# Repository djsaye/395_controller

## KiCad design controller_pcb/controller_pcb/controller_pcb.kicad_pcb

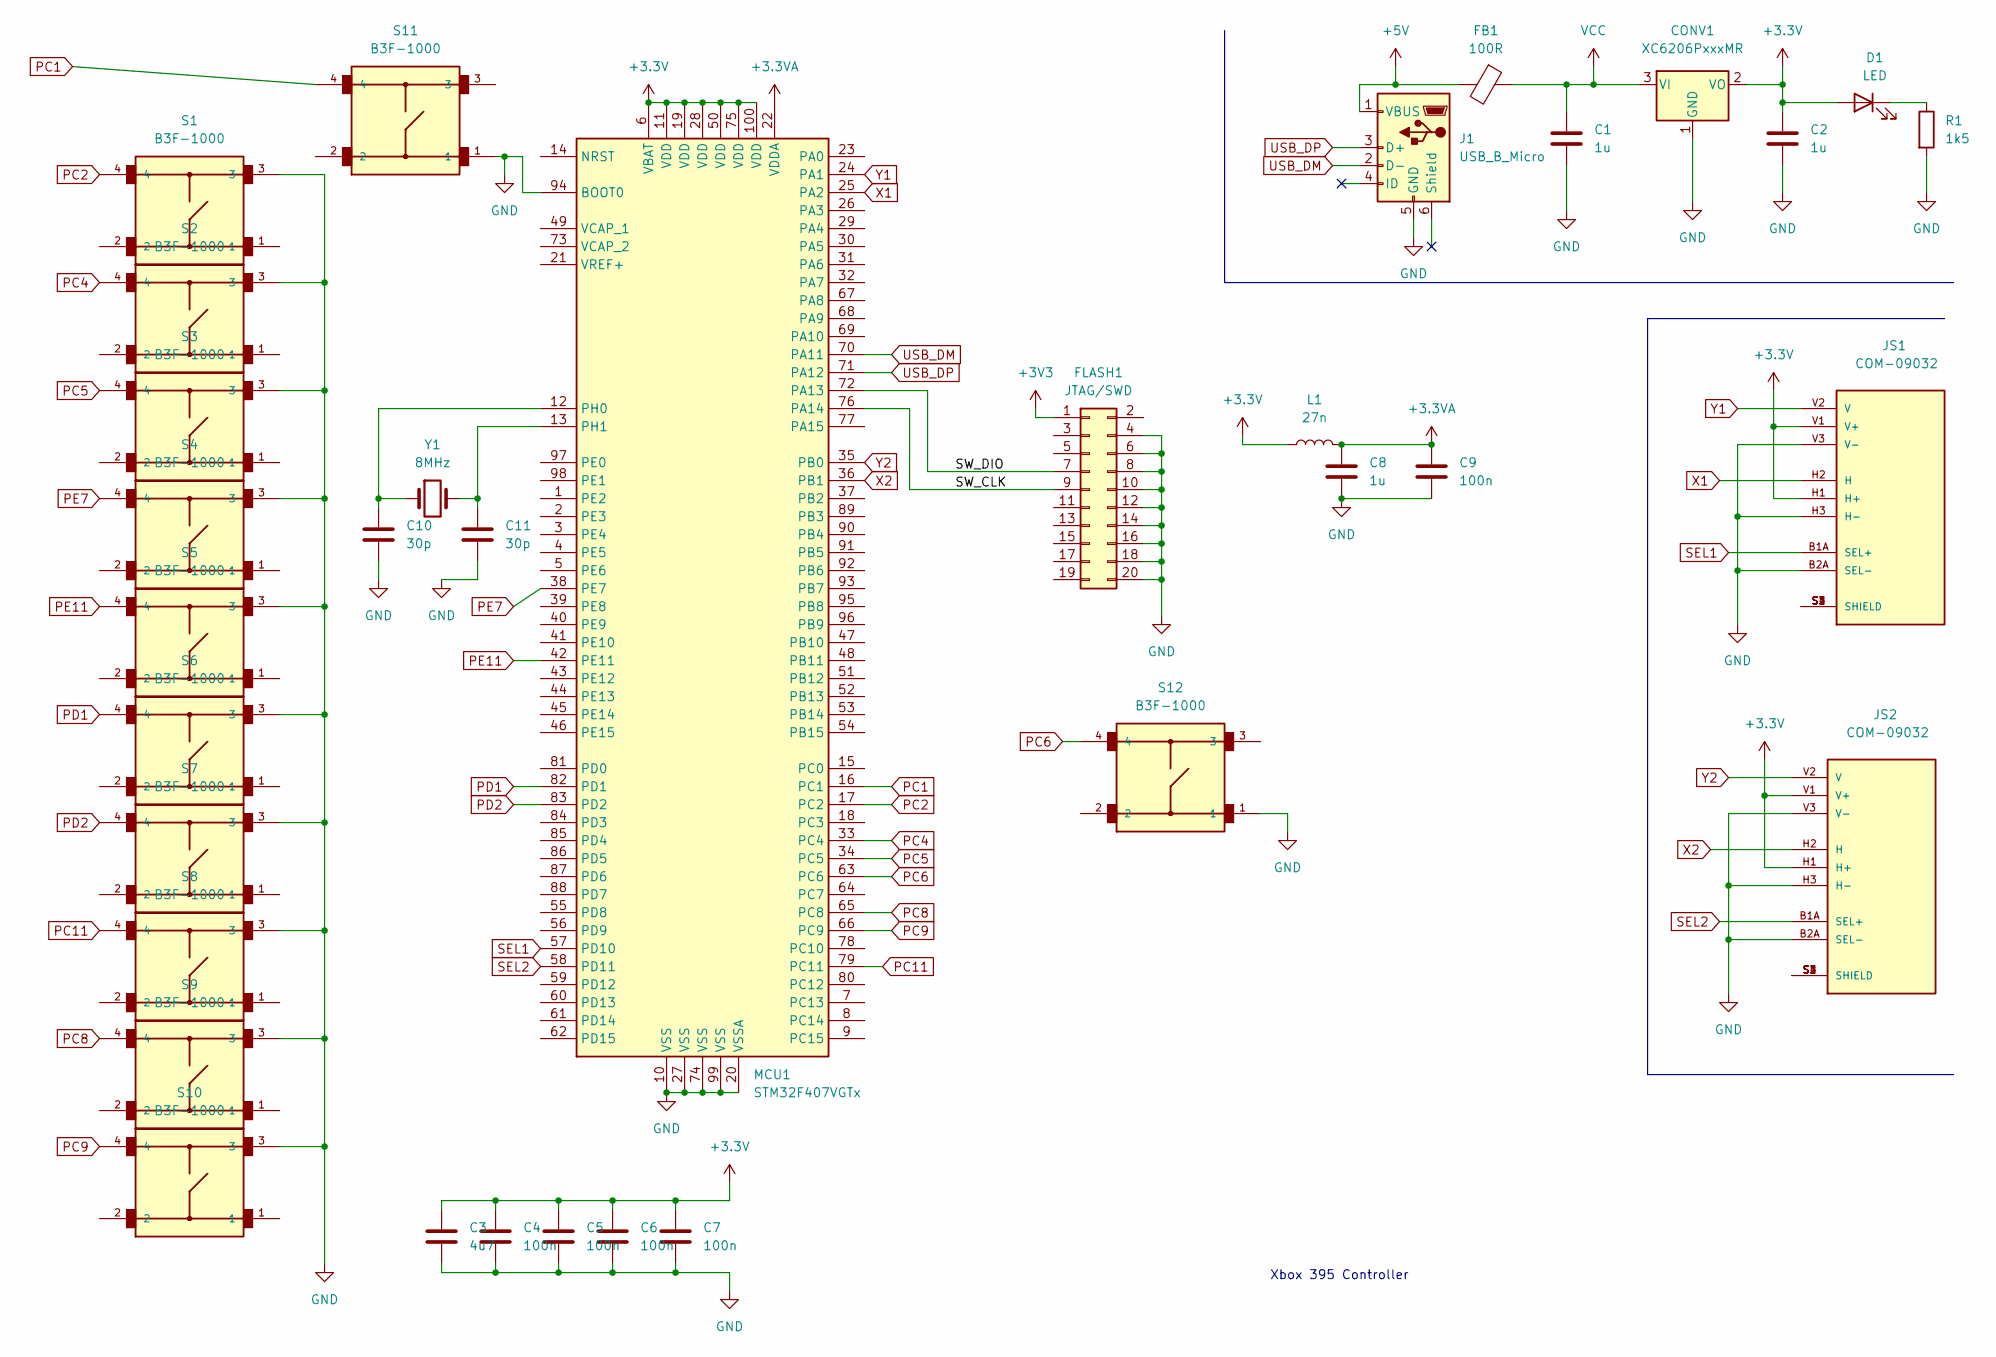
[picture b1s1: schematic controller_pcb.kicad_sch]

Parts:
C1, C2, C8: 1u; C_0805_2012Metric
C3: 4u7; C_0805_2012Metric
C4, C5, C6, C7, C9: 100n; C_0805_2012Metric
C10, C11: 30p; C_0805_2012Metric
CONV1: XC6206PxxxMR; SOT-23
D1: LED; D_0603_1608Metric
FB1: 100R; R_0805_2012Metric
FLASH1: JTAG/SWD; PinHeader_2x10_P2.54mm_Vertical
J1: USB_B_Micro; USB_Micro-B_Wuerth_629105150521
JS1, JS2: COM-09032; XDCR_COM-09032; PARTREV N/A
L1: 27n; L_0402_1005Metric
MCU1: STM32F407VGTx; LQFP-100_14x14mm_P0.5mm
R1: 1k5; R_0805_2012Metric
S1, S2, S3, S4, S5, S6, S7, S8, S9, S10, S11, S12: B3F-1000; SW_B3F-1000
Y1: 8MHz; Crystal_SMD_5032-2Pin_5.0x3.2mm

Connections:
+3.3VA: C8.1, C9.1, L1.2, MCU1.22 (VDDA)
+5V: FB1.2, J1.1 (VBUS)
/SW_CLK: FLASH1.9, MCU1.76 (PA14)
/SW_DIO: FLASH1.7, MCU1.72 (PA13)
GND: C1.2, C2.2, C3.2, C4.2, C5.2, C6.2, C7.2, C8.2, C9.2, C10.2, C11.2, CONV1.1 (GND), FLASH1.4, FLASH1.6, FLASH1.8, FLASH1.10, FLASH1.12, FLASH1.14, FLASH1.16, FLASH1.18, FLASH1.20, J1.5 (GND), JS1.B2A (SEL-), JS1.H3 (H-), JS1.V3 (V-), JS2.B2A (SEL-), JS2.H3 (H-), JS2.V3 (V-), MCU1.10 (VSS), MCU1.20 (VSSA), MCU1.27 (VSS), MCU1.74 (VSS), MCU1.94 (BOOT0), MCU1.99 (VSS), R1.2, S1.3, S2.3, S3.3, S4.3, S5.3, S6.3, S7.3, S8.3, S9.3, S10.3, S11.1, S12.1
unnamed: C10.1, MCU1.12 (PH0), Y1.1
unnamed: C11.1, MCU1.13 (PH1), Y1.2
unnamed: D1.1 (K), R1.1
unnamed: JS1.S1 (SHIELD), JS1.S2 (SHIELD), JS1.S3 (SHIELD), JS1.S4 (SHIELD)
unnamed: JS2.S1 (SHIELD), JS2.S2 (SHIELD), JS2.S3 (SHIELD), JS2.S4 (SHIELD)
PC1: MCU1.16 (PC1), S11.4
PC2: MCU1.17 (PC2), S1.4
PC4: MCU1.33 (PC4), S2.4
PC5: MCU1.34 (PC5), S3.4
PC6: MCU1.63 (PC6), S12.4
PC8: MCU1.65 (PC8), S9.4
PC9: MCU1.66 (PC9), S10.4
PC11: MCU1.79 (PC11), S8.4
PD1: MCU1.82 (PD1), S6.4
PD2: MCU1.83 (PD2), S7.4
PE7: MCU1.38 (PE7), S4.4
PE11: MCU1.42 (PE11), S5.4
SEL1: JS1.B1A (SEL+), MCU1.57 (PD10)
SEL2: JS2.B1A (SEL+), MCU1.58 (PD11)
USB_DM: J1.2 (D-), MCU1.70 (PA11)
USB_DP: J1.3 (D+), MCU1.71 (PA12)
VCC: C1.1, CONV1.3 (VI), FB1.1
X1: JS1.H2 (H), MCU1.25 (PA2)
X2: JS2.H2 (H), MCU1.36 (PB1)
Y1: JS1.V2 (V), MCU1.24 (PA1)
Y2: JS2.V2 (V), MCU1.35 (PB0)

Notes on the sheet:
Xbox 395 Controller

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
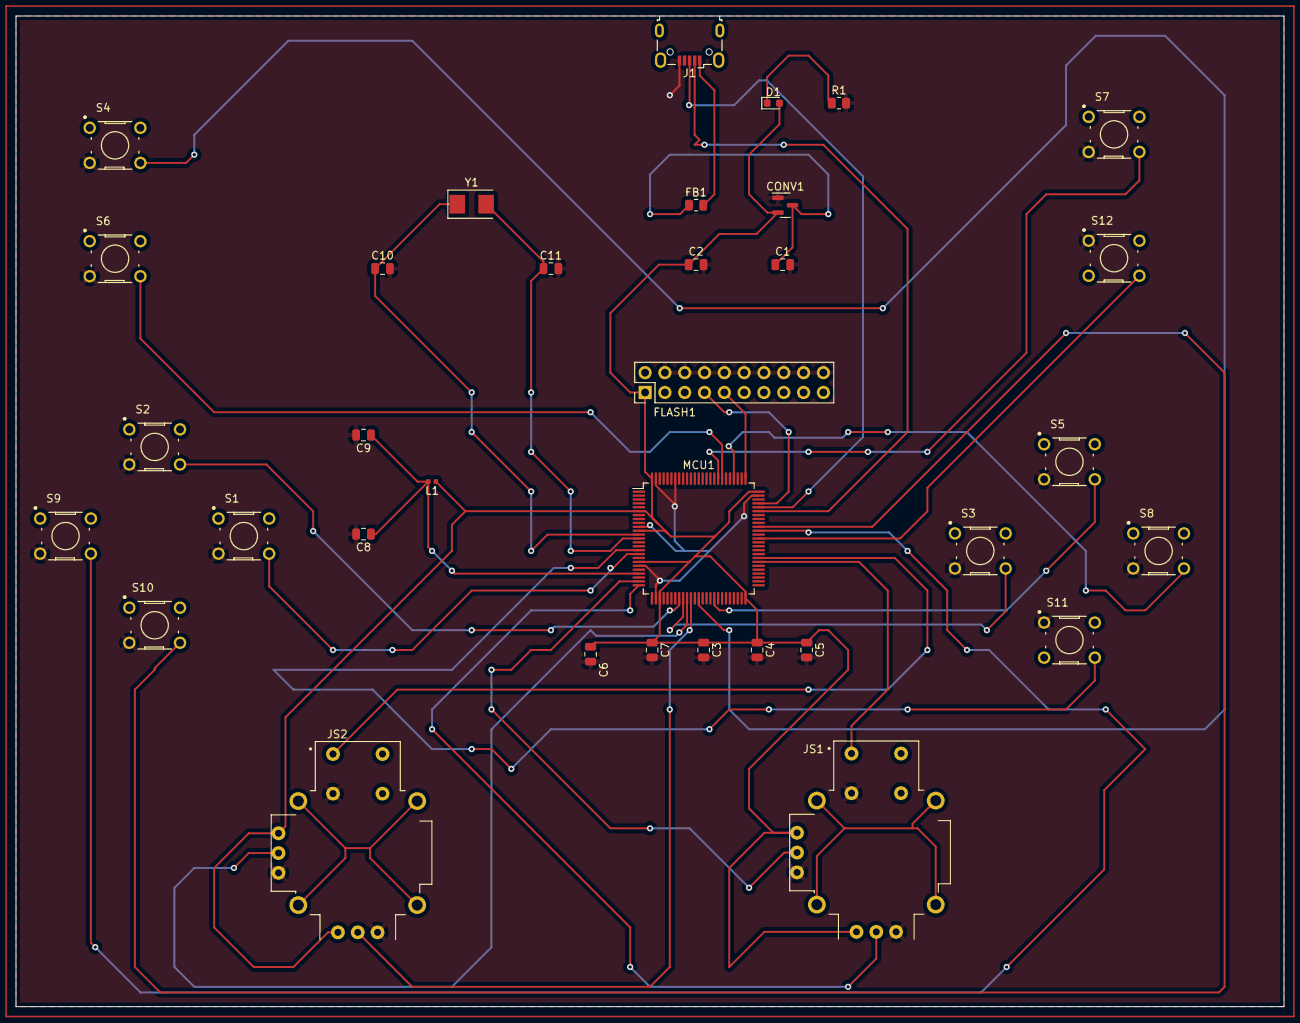
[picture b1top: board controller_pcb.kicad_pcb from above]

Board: 2 copper layers, 162.6 x 127.0 mm, 34 parts (0 on the bottom side), 32 nets.

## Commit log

2023-02-14 adding project
2023-02-21 added new changes to make usb into normal HID
2023-02-27 Got windows to show buttons and axis values on the gamepad tester
2023-02-27 started pcb project
2023-02-27 couple of changes
2023-02-28 Added USB and SW Connector
2023-03-01 added one button
2023-03-01 Got the buttons to work on the windows side of things
2023-03-06 added all but one buttons
2023-03-07 changed port assignments
2023-03-07 added joystick controller symbol
2023-03-07 didnt save
2023-03-21 I think schematic is done...
2023-03-21 assigning footprints
2023-03-28 Finished Footprints
2023-03-30 Adding code for Joystick
2023-03-30 have to draw pcb
2023-03-30 Updated PCB
2023-04-04 started wiring schematic
2023-04-05 random update
2023-04-05 finalized pcb layout, no edges have been made
2023-04-05 small change
2023-04-05 finialized pcb arrangment
2023-04-06 Created the layers
2023-04-11 Added vias for GND pins
2023-04-11 Created GND layer correctly
2023-04-11 did some stuff
2023-04-11 Changed DRC settings
2023-04-11 added the easy routes lol
2023-04-14 working on joystick
2023-04-14 Got joystick to behave properly, still need to send through usb
2023-04-14 initial wiring done
2023-04-14 Fixed some right angles
2023-04-14 almost done w traces
2023-04-14 fixed drc warnings and errors in pcb
2023-04-15 moved silkscreen
2023-04-17 Made a small GND connection to USB Micro
2023-04-18 Got joystick to show correct values on the PC
